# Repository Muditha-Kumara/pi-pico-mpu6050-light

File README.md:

# Motion Light Pico Hat

An interactive dual-core LED "water flow" and tilt simulation for the Raspberry Pi Pico / Pico 2 using a WS2812B LED strip and an MPU-6050 IMU (or a built‑in software tilt simulator when the sensor is absent). The project demonstrates:

- Dual-core coordination on RP2040 (Core 0: sensor / simulation; Core 1: LED rendering + serial output)
- Smooth physics-like motion (velocity, damping, bounce) converted to a glowing LED blob that shifts and reflects within the strip
- ASCII real-time visualization in the Serial Monitor for debugging without LEDs
- Seamless fallback to simulated tilt if the accelerometer is not detected

## Supported Boards

| Board                      | PlatformIO Environment | Arduino IDE Board                        | Notes                                      |
|----------------------------|------------------------|------------------------------------------|--------------------------------------------|
| Raspberry Pi Pico (RP2040) | `pico_official`        | "Raspberry Pi Pico" (Earle Philhower core) | Fully supported                            |
| Raspberry Pi Pico 2 (RP2350) | `rpipico2_project`      | "Raspberry Pi Pico 2" (Earle Philhower core) | Use with updated RP2350 core; see below    |

*Pico 2 support uses the RP2350 chip. Logic and pin usage are identical. To enable, adjust `platformio.ini` and ensure the correct board/platform is selected.*

> **Development Note:**
> This project was requested for the original Raspberry Pi Pico (RP2040). However, all development and testing were performed on a Raspberry Pi Pico 2 (RP2350) board. The code is fully compatible with the normal Pico board and was written to ensure it works on both models. If you use a Pico 2, select the correct environment in [`platformio.ini`](./platformio.ini) or Arduino IDE as described above.

## Features

- Real-time LED physics (position, velocity, damping, reflection)
- Adaptive glow with Gaussian/exponential falloff and shimmer
- Dual-core separation: deterministic LED refresh at ~30 FPS independent of sensor loop (~50 Hz)
- Automatic hardware detection for MPU‑6050 at I2C address `0x68`; simulation fallback if absent
- Lightweight inter-core communication (volatile globals)

## Directory Structure

```
.
├── platformio.ini      # PlatformIO build configuration
├── src/
│   └── main.cpp        # Main application source (dual-core logic, PlatformIO)
├── MotionLightPicoHat_Arduino/
│   └── MotionLightPicoHat_Arduino.ino # Arduino IDE-friendly sketch (identical logic)
├── lib/                # (Optional) user libraries
├── include/            # (Optional) project headers
├── PCB/                # Hardware design files and outputs
│   ├── pico.kicad_sch      # KiCad schematic
│   ├── pico.kicad_pcb      # KiCad PCB layout
│   ├── pico.kicad_pro      # KiCad project settings
│   ├── pico.kicad_prl      # KiCad project local settings (ignore in git)
│   ├── PCB_Print/          # Gerber and drill files for manufacturing
│   │   └── pico-PCB(gbr).zip # Gerber/drill manufacturing archive for PCB fabrication
│   └── Assets/             # PCB-related images and logos
├── assets/             # Icons and images for documentation
├── README.md           # This documentation
├── LICENSE             # Project license
```

- [`MotionLightPicoHat_Arduino/`](./MotionLightPicoHat_Arduino/.) contains an Arduino IDE-friendly [`.ino`](./MotionLightPicoHat_Arduino/MotionLightPicoHat_Arduino.ino) file for easy use. Open this folder and file directly in Arduino IDE for the same functionality as [`src/main.cpp`](./src/main.cpp).

- [`PCB/`](./PCB/) contains all hardware design files: schematic, PCB layout, project settings, gerbers (in [`PCB_Print/`](./PCB/PCB_Print/)) and images.

## Hardware Requirements
## PCB Details
#### I2C Address Selection

The PCB includes a J4 jumper, which can be used to select the I2C address of the MPU-6050 sensor. By bridging or leaving J4 open, you can choose between the two standard MPU-6050 I2C addresses (0x68 or 0x69). Refer to the silkscreen and schematic for the correct configuration for your sensor module.

**Note:** The PCB is designed specifically for the original Raspberry Pi Pico (RP2040), not Pico 2. Pinout and mechanical fit are for the standard Pico board only.

This project includes a custom PCB designed for the Raspberry Pi Pico, WS2812B LED strip, and MPU-6050 IMU. The PCB provides:

- Direct Pico header footprint (solder Pico)
- Onboard or external MPU-6050 support (I2C)
- Dedicated LED strip connector (5V, GND, DIN)
- 5V power input (max 5A) and distribution
- Clear silkscreen labels for all connections

### PCB Images

**Top View (Silkscreen):**

**Bottom View (Component Side):**

> _Images above: Top shows silkscreen labels and external connections; bottom shows Pico header, MPU-6050 footprint, and connectors._

### Key Connections

- **External MPU-6050:**
   - GND, VCC, SDA, SCL pins for external IMU module
- **LED Connection:**
   - 5VDC Out, Din (GPIO 22), GND for WS2812B strip
- **5VDC In:**
   - Main power input for LEDs and Pico
- **Pico USB:**
   - For programming and optional power

### Assembly Notes

- Ensure correct orientation of the Pico and all connectors.
- Use the onboard or external MPU-6050 as needed.
- Always connect GND between Pico, LED strip, and power supply.

PCB design files and [Gerbers](./PCB/PCB_Print/pico-PCB(gbr).zip) are in the [`PCB/`](./PCB/.) directory for manufacturing or modification.

| Component | Purpose | Notes |
|-----------|---------|-------|
| Raspberry Pi Pico| MCU | USB power + programming |
| WS2812B LED strip (30 LEDs) | Visual effect | Data pin connected to GPIO 22 |
| MPU-6050 IMU (optional) | Tilt sensing | I2C at `0x68` on GPIO 4 (SDA) and GPIO 5 (SCL) |
| Power supply (5V recommended) | LED power | Ensure common ground with Pico |

### Pin Mapping

| Signal | RP2040 GPIO | Description |
|--------|-------------|-------------|
| LED Data | 22 | WS2812B DIN |
| I2C SDA | 4 | MPU-6050 SDA |
| I2C SCL | 5 | MPU-6050 SCL |

## Software Dependencies

- [FastLED](https://github.com/FastLED/FastLED) (≥3.10.x) for LED control
- Wire (built-in with Arduino core) for I2C communication

Optional: Adafruit MPU6050 library is **not required** because raw register reads are used for robustness and minimal overhead.

## Serial Output Compatibility (PlatformIO vs Arduino IDE)

The code supports both single-line (overwriting) and multi-line serial output for compatibility with different serial monitors:

- **Single-line output** (default, works in PlatformIO and most advanced terminals):
   - Set `#define USE_CARRIAGE_RETURN 1` at the top of [`src/main.cpp`](./src/main.cpp).
   - Output will always overwrite the same line, giving a live-updating effect.
- **Multi-line output** (for Arduino IDE Serial Monitor):
   - Set `#define USE_CARRIAGE_RETURN 0` at the top of [`src/main.cpp`](./src/main.cpp).
   - Each update prints on a new line (Arduino IDE Serial Monitor does not support carriage return overwrite).

**How to switch:**

```cpp
#define USE_CARRIAGE_RETURN 1 // or 0 for Arduino IDE
```

This macro is at the top of [`src/main.cpp`](./src/main.cpp). Change it as needed for your environment.

## Dual-Core Flow Overview

| Core | Function | Key Loop Rate |
|------|----------|---------------|
| Core 0 (`setup()` / `loop()`) | I2C sensor read or simulation | ~50 Hz (20 ms delay) |
| Core 1 (`setup1()` / `loop1()`) | LED physics + rendering + ASCII output | ~30 FPS (33 ms delay) |

Synchronization uses simple `volatile` variables (`g_tilt_x`, `g_sensor_connected`). For production-grade systems with higher complexity, use mutexes or queues.

## Building with PlatformIO

### 1. Prerequisites

- PlatformIO Core or VS Code + PlatformIO extension installed

### 2. Key [`platformio.ini`](./platformio.ini) Excerpt

```ini
[env:pico_official]
platform = https://github.com/maxgerhardt/platform-raspberrypi.git
board = pico
framework = arduino
board_build.core = earlephilhower
monitor_speed = 115200
lib_deps = Wire, FastLED

[env:rpipico2_project]
platform = https://github.com/maxgerhardt/platform-raspberrypi.git
board = rpipico2
framework = arduino
board_build.core = earlephilhower
monitor_speed = 115200
lib_deps =Wire, FastLED
```

### 3. Build & Upload

```bash
# Build
platformio run -e pico_official

# (Optional) Clean
platformio run -e pico_official -t clean

# Upload (UF2 drag-and-drop or configured uploader)
platformio run -e pico_official -t upload
```

If using UF2: hold BOOTSEL while plugging the Pico, then copy the generated `firmware.uf2` from `.pio/build/pico_official/` to the mounted drive.

### 4. Monitor Serial Output

```bash
platformio device monitor -e pico_official --baud 115200
```

You will see a single updating line like:

```text
[H/W] Tilt (X): -0.12 | Pos: 15.44 | Flow: [   __====~~~~====__   ]
```

`[SIM]` indicates the fallback simulation mode when the sensor is absent.

## Using Arduino IDE Instead

1. Open Arduino IDE (2.x recommended).
2. Preferences → Additional Boards Manager URLs:
   - `https://github.com/earlephilhower/arduino-pico/releases/download/global/package_rp2040_index.json`
3. Boards Manager: install "RP2040" (Earle Philhower).
4. Board: Tools → Board → Raspberry Pi RP2040 Boards → Raspberry Pi Pico (or Pico 2).
5. Open [`MotionLightPicoHat_Arduino/MotionLightPicoHat_Arduino.ino`](./MotionLightPicoHat_Arduino/MotionLightPicoHat_Arduino.ino) directly in Arduino IDE (recommended), or copy code from [`src/main.cpp`](./src/main.cpp) if you want to create your own sketch. Both files are kept in sync and provide the same functionality (including dual-core support with `setup1()` / `loop1()`).
6. Library Manager: install FastLED.
7. Upload:
   - Default: Hold BOOTSEL, plug in, then Upload.
   - Optional: Select Picotool method if installed.
8. Open Serial Monitor @ 115200 baud.

## LED Animation Logic

1. Read tilt acceleration (real or simulated) → scaled to influence velocity.
2. Apply damping & clamp velocity.
3. Integrate velocity → position of the "water mass".
4. Bounce at ends with energy loss (`BOUNCE_DAMPING`).
5. Glow profile: `intensity = exp(-distance * GLOW_DECAY)` plus shimmer sine term.
6. Map intensity to color scaling on `CRGB WATER_COLOR`.

## Extending the Project

| Idea | Description |
|------|-------------|
| Add Y/Z tilt | Expand to 2D matrix or color modulation |
| Sensor fusion | Incorporate complementary filter for stable angles |
| Persistent config | Store brightness or mode in flash/EEPROM |
| Multi-effect engine | Switch between "water", "fire", "sparkle" modes via serial commands |

## Troubleshooting

| Symptom | Possible Cause | Fix |
|---------|----------------|-----|
| `Arduino.h` missing (PlatformIO) | Wrong platform core | Use Earle Philhower core via custom platform URL as shown |
| All LEDs off | Power issue or brightness too low | Confirm 5V supply & `FastLED.setBrightness()` value |
| `[SIM]` always shown | Sensor not detected | Check wiring, address `0x68`, pull-ups on SDA/SCL |
| Flickering LEDs | Long wires or insufficient grounding | Add data line resistor (~330Ω), ensure shared ground |
| Serial gibberish | Baud mismatch | Use 115200 in monitor |

## Performance Notes

- RAM usage is minimal (<5%), leaving headroom for additional features.
- Using software glow math with simple `exp()` calls; performance acceptable for 30 LEDs at 30 FPS.
- FastLED auto-selects software SPI timing for WS2812B (normal).

## Safety & Power Considerations

- At full white, WS2812B LED strips can draw ~60mA/LED. This animation uses modest brightness (blue tint) but plan power budget (e.g., 30 LEDs ≈ 1.8A worst case).
- Always share ground between Pico and LED power.

## License

Add your chosen license (e.g., MIT, Apache-2.0) here. Example MIT header:

```text
Copyright (c) 2025 <Muditha Chinthana Kumara>
Permission is hereby granted, free of charge, to any person obtaining a copy...
```

## Acknowledgements

- Earle Philhower RP2040 Arduino core
- FastLED community
- Documentation generated with AI assistance (GitHub Copilot)

---

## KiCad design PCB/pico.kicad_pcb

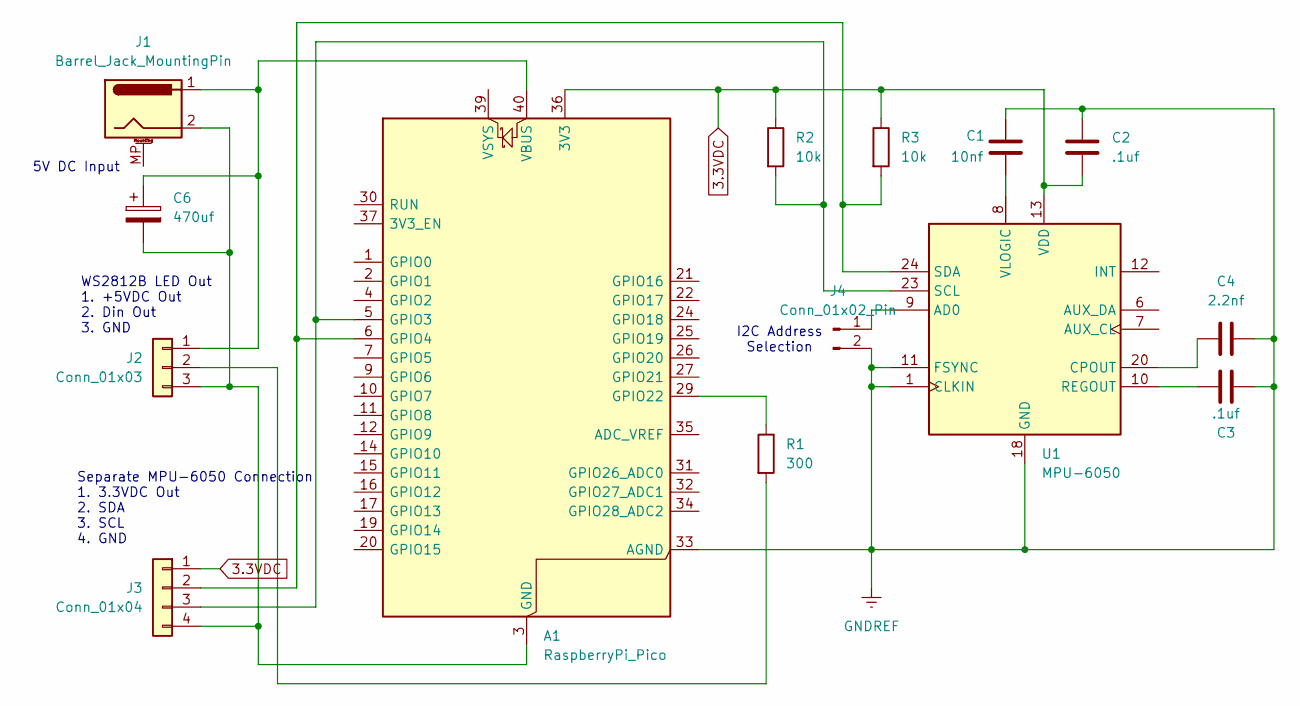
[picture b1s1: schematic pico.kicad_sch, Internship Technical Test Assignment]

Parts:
A1: RaspberryPi_Pico; RaspberryPi_Pico_Common_SMD
C1: 10nf; C_0805_2012Metric
C2, C3: .1uf; C_0805_2012Metric
C4: 2.2nf; C_0805_2012Metric
C6: 470uf; CP_Radial_D8.0mm_P2.50mm
J1: Barrel_Jack_MountingPin; BarrelJack_CUI_PJ-063AH_Horizontal
J2: Conn_01x03; JST_PH_S3B-PH-K_1x03_P2.00mm_Horizontal
J3: Conn_01x04; JST_PH_S4B-PH-K_1x04_P2.00mm_Horizontal
J4: Conn_01x02_Pin; PinHeader_1x02_P2.54mm_Vertical
R1: 300; C_0805_2012Metric
R2, R3: 10k; C_0805_2012Metric
U1: MPU-6050; HVQFN-24-1EP_4x4mm_P0.5mm_EP2.1x2.1mm

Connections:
3.3VDC: A1.36 (3V3), C2.2, J3.1, R2.1, R3.1, U1.13 (VDD)
GNDREF: A1.33 (AGND), C1.1, C2.1, C3.1, C4.1, J4.2, U1.1 (CLKIN), U1.11 (FSYNC), U1.18 (GND)
unnamed: A1.5 (GPIO3), J3.3, R2.2, U1.23 (SCL)
unnamed: A1.6 (GPIO4), J3.2, R3.2, U1.24 (SDA)
unnamed: A1.29 (GPIO22), R1.1
unnamed: A1.40 (VBUS), C6.1, J1.1, J2.1
unnamed: J2.2, R1.2
unnamed: A1.3 (GND), A1.8 (GND), A1.13 (GND), A1.18 (GND), A1.23 (GND), A1.28 (GND), A1.38 (GND), C6.2, J1.2, J2.3, J3.4
unnamed: J4.1, U1.9 (AD0)
unnamed: C4.2, U1.20 (CPOUT)
unnamed: C3.2, U1.10 (REGOUT)
unnamed: C1.2, U1.8 (VLOGIC)

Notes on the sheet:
I2C Address Selection
5V DC Input
WS2812B LED Out 1. +5VDC Out 2. Din Out 3. GND
Separate MPU-6050 Connection 1. 3.3VDC Out 2. SDA 3. SCL 4. GND

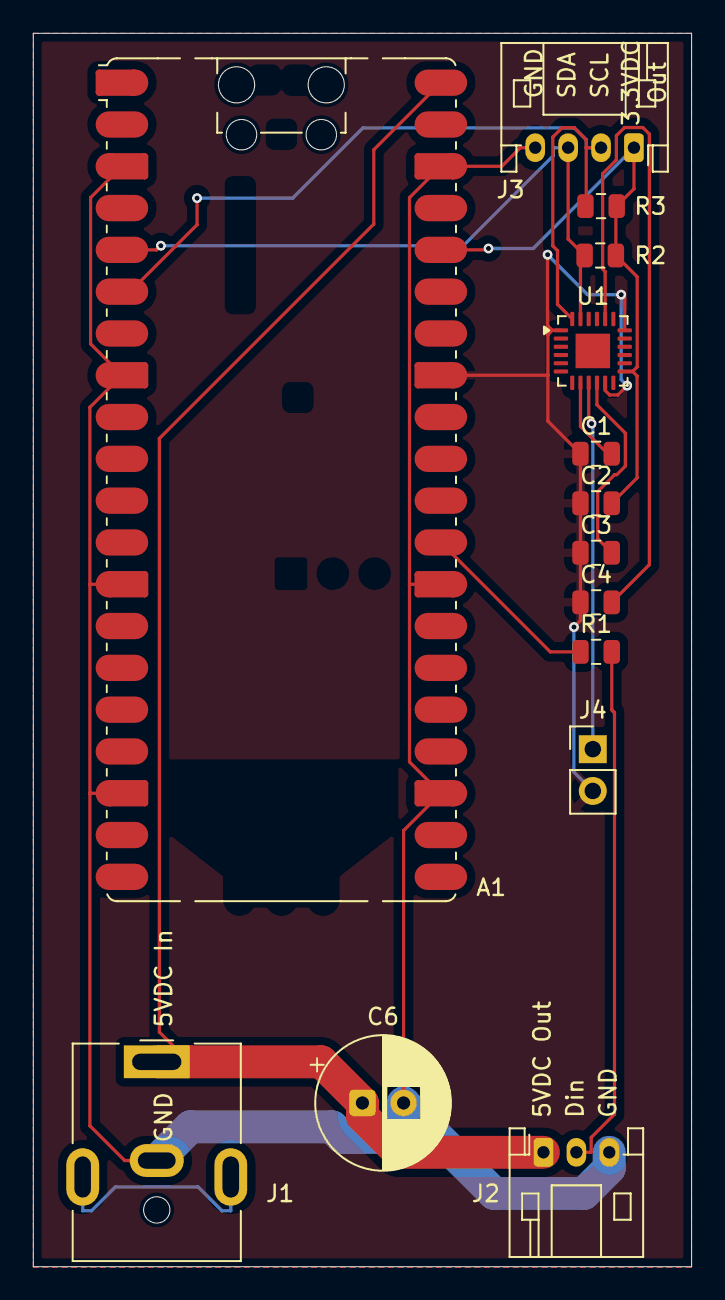
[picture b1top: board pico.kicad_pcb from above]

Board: 2 copper layers, 40.0 x 75.0 mm, 14 parts (0 on the bottom side), 12 nets.

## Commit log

2025-11-24 Add PCB design files for project hardware
2025-11-25 Add Version !.0
2025-11-27 Ready for final submition
2025-11-29 add basic program
2025-11-29 modify gitignore
2025-11-30 add .ino file
2025-11-30 Add PCB details and assembly notes to README.md
2025-11-30 add pcb image and link
2025-12-01 Update board and library information in the Arduino file
2025-12-01 Update README.md for improved link formatting and clarity
2025-12-01 Update README.md for improved clarity and formatting of links
